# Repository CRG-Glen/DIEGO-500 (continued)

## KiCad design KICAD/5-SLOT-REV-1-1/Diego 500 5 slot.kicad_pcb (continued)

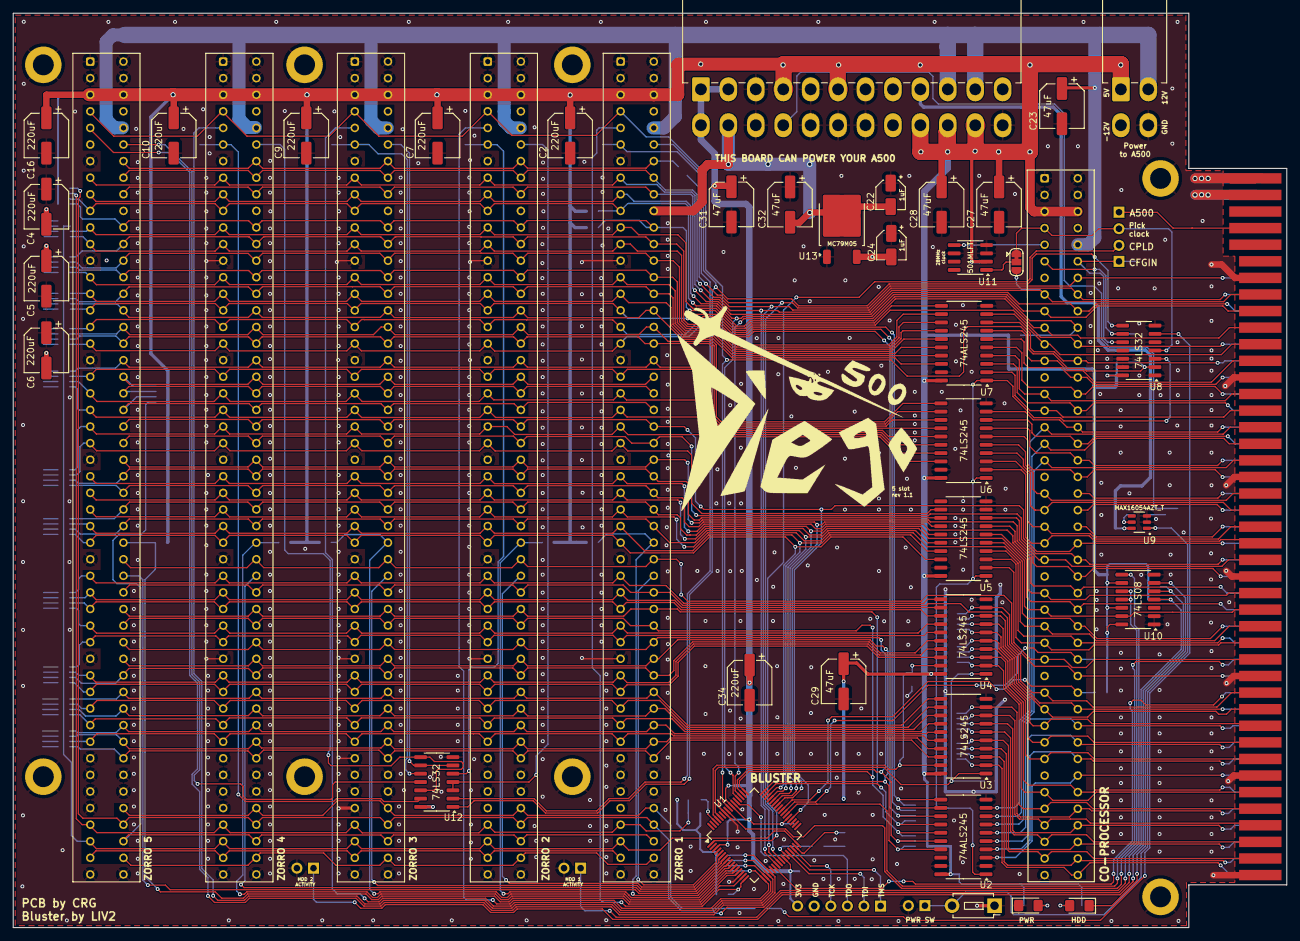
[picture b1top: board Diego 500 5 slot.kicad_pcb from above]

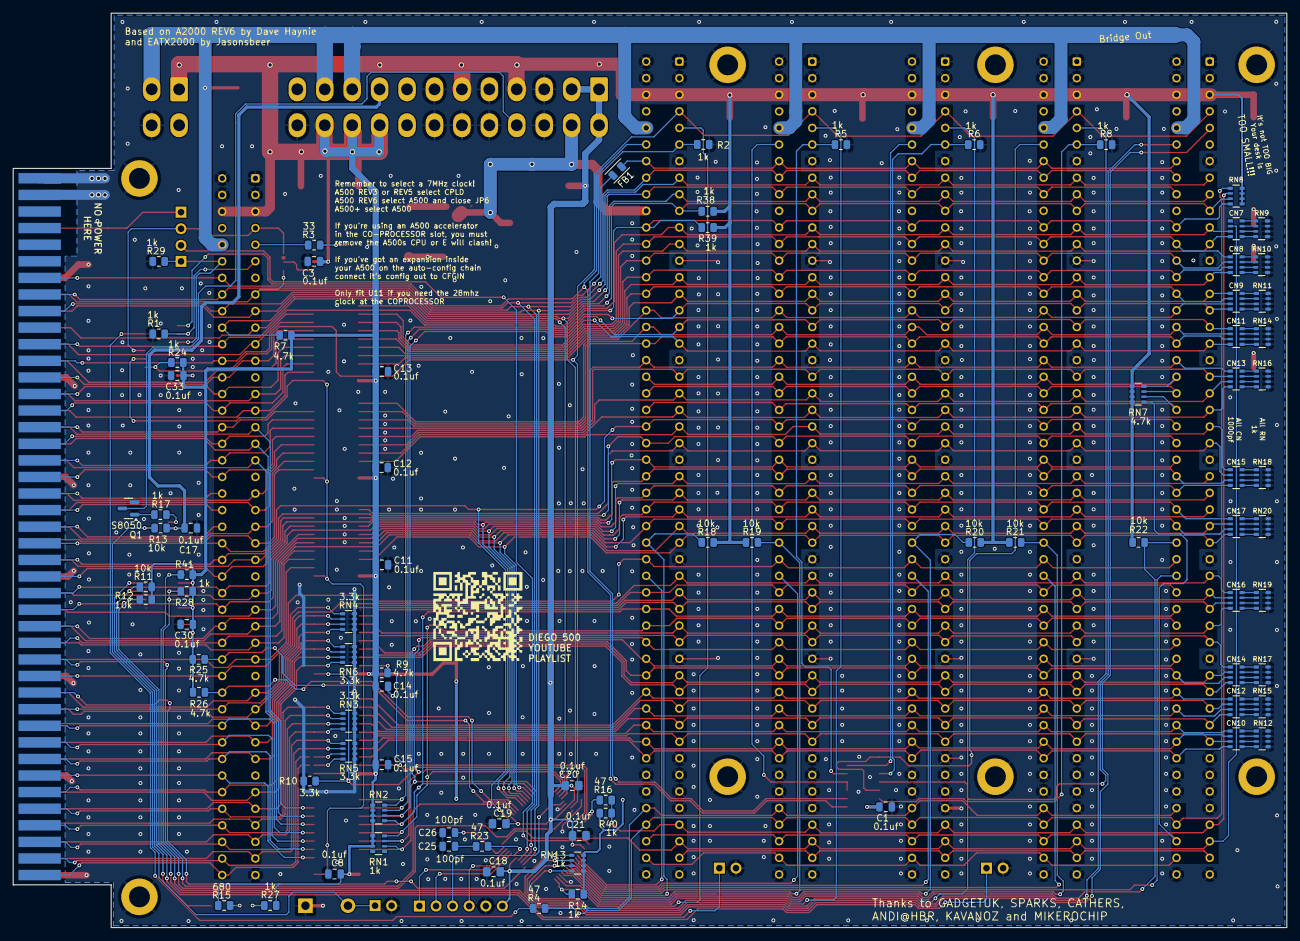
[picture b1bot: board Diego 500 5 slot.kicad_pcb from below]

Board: 4 copper layers, 195.0 x 140.0 mm, 140 parts (83 on the bottom side), 230 nets.

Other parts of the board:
R38, R39, R40, R41: 1k; R_0805_2012Metric

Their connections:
+5V: R38.1, R39.1, R40.1, R41.1; also elsewhere on the board
DOE: R40.2; also elsewhere on the board
_BusRST: R41.2; also elsewhere on the board
_INT2: R38.2; also elsewhere on the board
_INT6: R39.2; also elsewhere on the board
